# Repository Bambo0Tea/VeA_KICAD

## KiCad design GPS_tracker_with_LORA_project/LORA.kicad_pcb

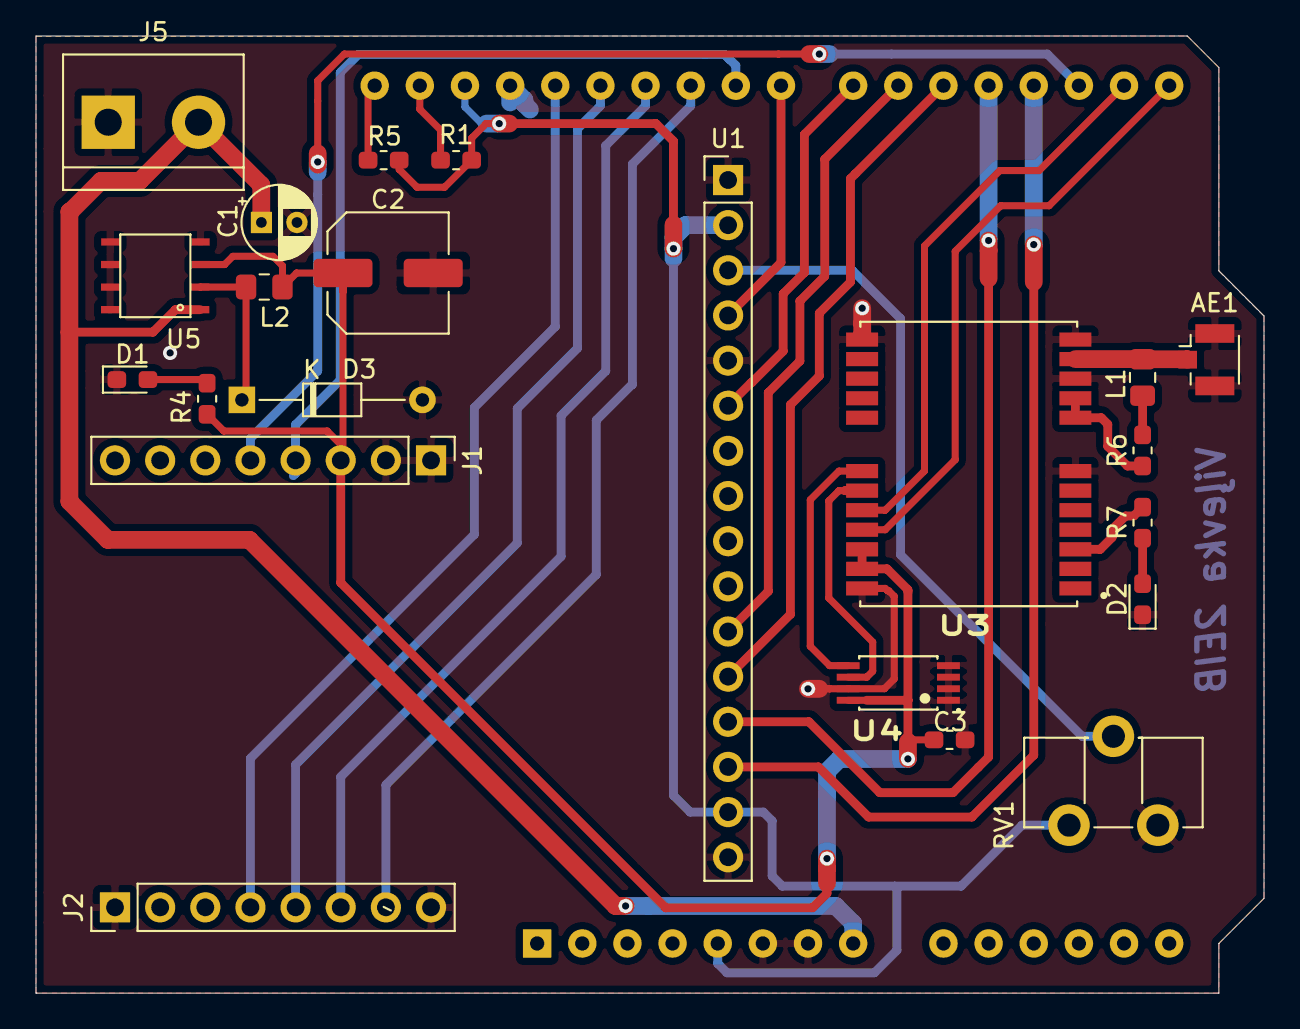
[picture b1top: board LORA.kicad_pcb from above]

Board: 2 copper layers, 69.1 x 53.8 mm, 23 parts (1 on the bottom side), 30 nets.

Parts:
A1: Arduino_UNO_R3
AE1: Antenna_Shield; U.FL_Hirose_U.FL-R-SMT-1_Vertical
C1: 680uF; CP_Radial_D4.0mm_P2.00mm
C2: 220uF; C_Elec_6.3x7.7
C3: 0.1uF; C_0603_1608Metric_Pad1.05x0.95mm_HandSolder
D1: 3V3; LED_0603_1608Metric_Pad1.05x0.95mm_HandSolder
D2: GPS; LED_0603_1608Metric_Pad1.05x0.95mm_HandSolder
D3: D_Schottky; D_DO-34_SOD68_P10.16mm_Horizontal
J1: LoRa Left; PinHeader_1x08_P2.54mm_Vertical
J2: Lora Right; PinHeader_1x08_P2.54mm_Vertical
J5: Power; TerminalBlock_bornier-2_P5.08mm
L1: 27uH; L_0805_2012Metric_Pad1.15x1.40mm_HandSolder
L2: 33uH; L_0805_2012Metric_Pad1.15x1.40mm_HandSolder
R1, R5: 10k; R_0603_1608Metric_Pad1.05x0.95mm_HandSolder
R4: 680R; R_0603_1608Metric_Pad1.05x0.95mm_HandSolder
R6: 22R; R_0603_1608Metric_Pad1.05x0.95mm_HandSolder
R7: 1k; R_0603_1608Metric_Pad1.05x0.95mm_HandSolder
RV1: R_POT; Potentiometer_ACP_CA9-H5_Horizontal
U1: LCD; PinHeader_1x16_P2.54mm_Vertical
U3: NEO-6M-GPS; XCVR_NEO-6M-GPS
U4: 24aa32a; SOP8P65_300X640X120L60X24N
U5: A307_3.3V; DC_DC_converter_a307

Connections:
+3.3V: C2.1, C3.1, J1.3, L2.2, R4.1, U3.22, U3.23, U4.8, U5.3
+5V: A1.5, A1.30, R1.2, R5.1, RV1.1, U1.2, U1.15
+9V: A1.8, C1.1, J5.2, U5.1
D2: A1.17, J1.5
D3: A1.18, U1.14
D4: A1.19, U1.13
D5: A1.20, U1.12
D6: A1.21, U1.11
D7: A1.22, U1.6
D8: A1.23, U1.4
D9: A1.24, J1.4
D10: A1.25, J2.7
D11: A1.26, J2.6
D12: A1.27, J2.5
D13: A1.28, J2.4
Earth: A1.6, A1.7, A1.29, AE1.2, C1.2, C2.2, C3.2, D1.1, D2.1, D3.2, J1.1, J1.2, J2.1, J2.8, J5.1, RV1.3, U1.1, U1.5, U1.16, U3.7, U3.10, U3.12, U3.13, U3.24, U4.1, U4.2, U4.3, U4.4, U4.7, U5.4, U5.5, U5.6, U5.7, U5.8
unnamed: A1.31, R1.1
unnamed: A1.32, R5.2
unnamed: AE1.1, L1.1, U3.11
unnamed: D1.2, R4.2
unnamed: D2.2, R7.1
unnamed: D3.1, L2.1, U5.2
unnamed: L1.2, R6.2
unnamed: R6.1, U3.8, U3.9
unnamed: R7.2, U3.3
unnamed: RV1.2, U1.3
RXD1: A1.15, U3.21
SCL2: U3.19, U4.6
SDA2: U3.18, U4.5
TXD1: A1.16, U3.20

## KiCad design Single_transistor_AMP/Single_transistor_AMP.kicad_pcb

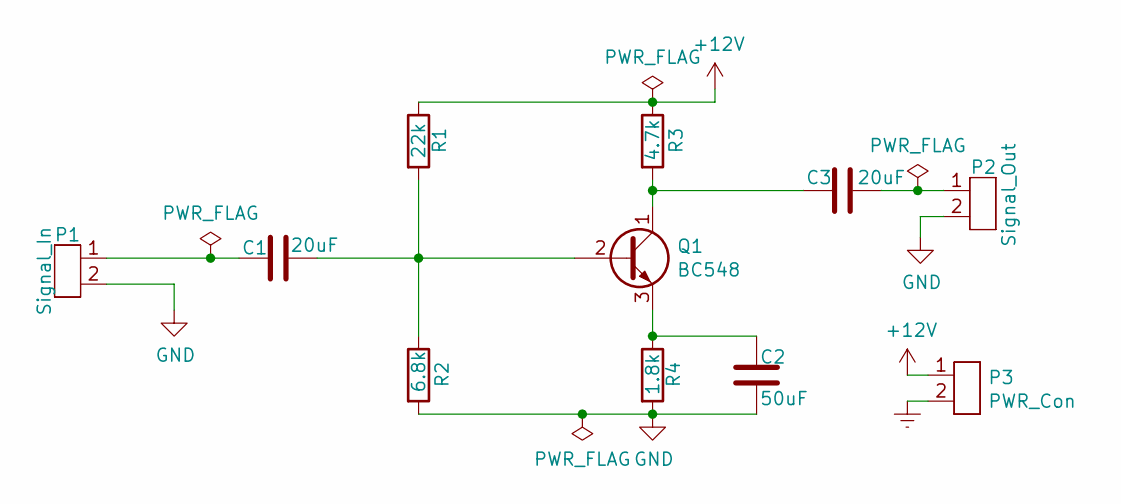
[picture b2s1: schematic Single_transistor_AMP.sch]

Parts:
C1, C3: 20uF; C_Disc_D5.0mm_W2.5mm_P5.00mm
C2: 50uF; C_Disc_D5.0mm_W2.5mm_P5.00mm
P1: Signal_In; SolderWire-0.5sqmm_1x02_P4.6mm_D0.9mm_OD2.1mm
P2: Signal_Out; SolderWire-0.5sqmm_1x02_P4.6mm_D0.9mm_OD2.1mm
P3: PWR_Con; Banana_Jack_2Pin
Q1: BC548; TO-92_Inline
R1: 22k; R_Axial_DIN0204_L3.6mm_D1.6mm_P5.08mm_Horizontal
R2: 6.8k; R_Axial_DIN0204_L3.6mm_D1.6mm_P7.62mm_Horizontal
R3: 4.7k; R_Axial_DIN0204_L3.6mm_D1.6mm_P7.62mm_Horizontal
R4: 1.8k; R_Axial_DIN0204_L3.6mm_D1.6mm_P7.62mm_Horizontal

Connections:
+12V: P3.1, R1.1, R3.1
Earth: P3.2
GND: C2.1, P1.2, P2.2, R2.2, R4.2
unnamed: C1.1, Q1.2 (B), R1.2, R2.1
unnamed: C1.2, P1.1
unnamed: C2.2, Q1.3 (E), R4.1
unnamed: C3.1, P2.1
unnamed: C3.2, Q1.1 (C), R3.2

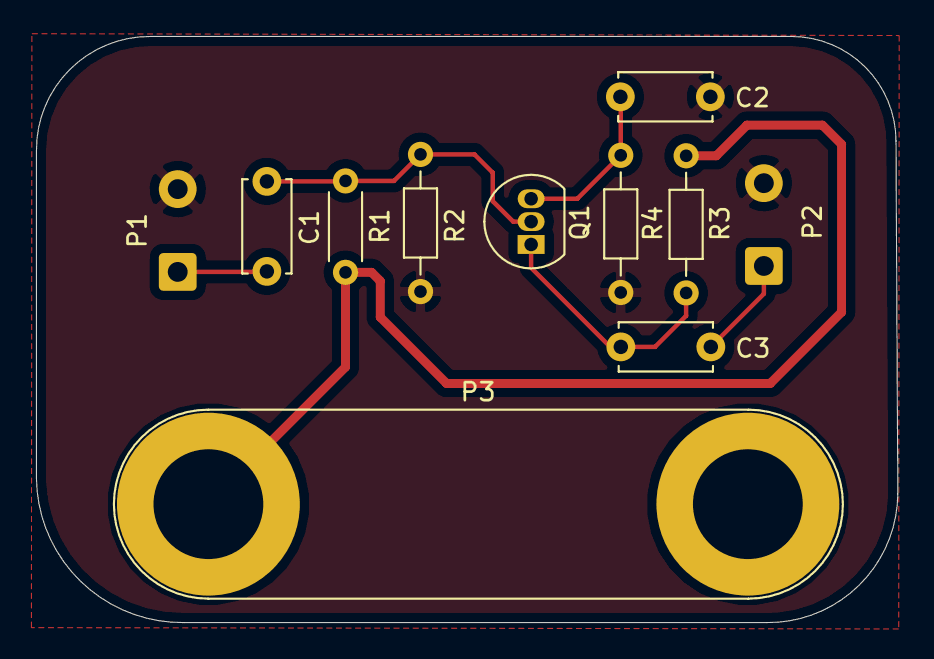
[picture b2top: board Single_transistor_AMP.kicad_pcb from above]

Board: 2 copper layers, 47.9 x 32.6 mm, 11 parts (0 on the bottom side), 7 nets.

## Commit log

2020-11-24 pepsi
2020-11-24 Pirmais MD
2020-11-24 Otrais MD
2020-11-24 PWR_Supply
2020-11-24 Single_transistor_AMP
2020-11-24 Work after III lecture
2020-11-24 Battery holders
2020-11-24 Trenin uzdevums pec IV lekcijas
2020-11-24 Battery holders HW
2020-11-25 Work after V lecture
2020-12-15 Work after VII lecture
2020-12-15 Work after IX lecture
2020-12-15 Work after X lecture
2020-12-15 Work after XII lecture
2021-01-03 Kursa darbs
2021-01-25 Kursa_Darbs
2021-01-26 Kursa darbs V2.0
